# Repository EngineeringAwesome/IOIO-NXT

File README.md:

IOIO-NXT
========

A circuit board that breaks out the pins on a IOIO-OTG to connect to the NXT Socket.

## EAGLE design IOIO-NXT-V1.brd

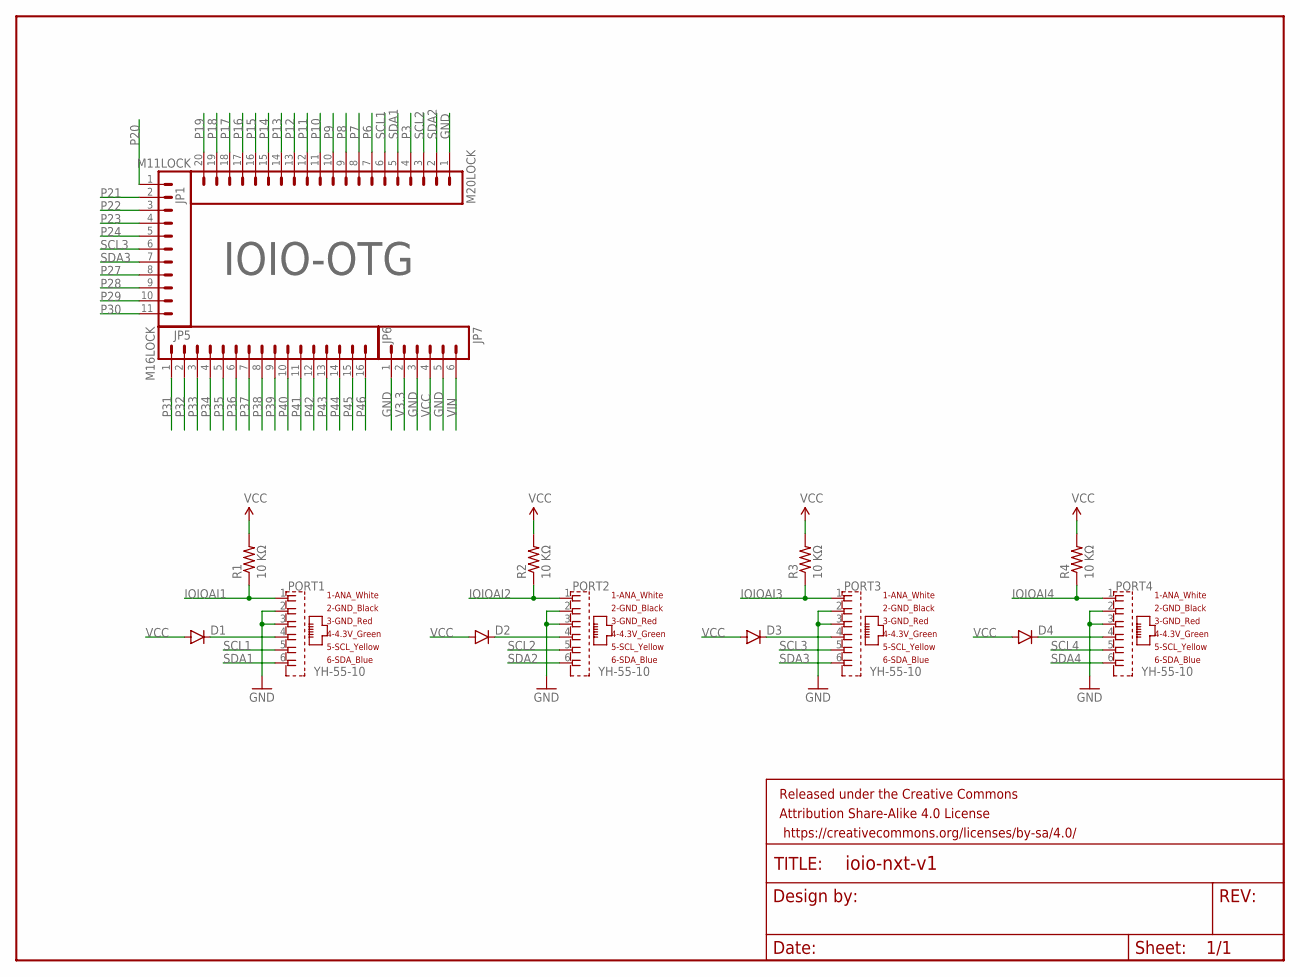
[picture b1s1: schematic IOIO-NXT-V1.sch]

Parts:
D1, D2, D3, D4: DIODE; DIODE-1N4001-KIT
FRAME1: FRAME-LETTER; CREATIVE_COMMONS
JP1: M20LOCK; 1X20_LOCK
JP5: M11LOCK; 1X11_LOCK
JP6: M16LOCK; 1X16_LOCK
JP7: M06LOCK; 1X06_LOCK
PORT1, PORT2, PORT3, PORT4: YH-55-10
R1, R2, R3, R4: 10 KΩ; AXIAL-0.4

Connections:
GND: JP1.1, JP7.1, JP7.3, JP7.5, PORT1.2 (2_GND_BLACK), PORT1.3 (3_GND_RED), PORT2.2 (2_GND_BLACK), PORT2.3 (3_GND_RED), PORT3.2 (2_GND_BLACK), PORT3.3 (3_GND_RED), PORT4.2 (2_GND_BLACK), PORT4.3 (3_GND_RED)
IOIOAI1: PORT1.1 (1_ANA_WHITE), R1.P$1 (1)
IOIOAI2: PORT2.1 (1_ANA_WHITE), R2.P$1 (1)
IOIOAI3: PORT3.1 (1_ANA_WHITE), R3.P$1 (1)
IOIOAI4: PORT4.1 (1_ANA_WHITE), R4.P$1 (1)
unnamed: D1.C, PORT1.4 (4_4.3V_GREEN)
unnamed: D4.C, PORT4.4 (4_4.3V_GREEN)
unnamed: D2.C, PORT2.4 (4_4.3V_GREEN)
unnamed: D3.C, PORT3.4 (4_4.3V_GREEN)
P3: JP1.4
P6: JP1.7
P7: JP1.8
P8: JP1.9
P9: JP1.10
P10: JP1.11
P11: JP1.12
P12: JP1.13
P13: JP1.14
P14: JP1.15
P15: JP1.16
P16: JP1.17
P17: JP1.18
P18: JP1.19
P19: JP1.20
P20: JP5.1
P21: JP5.2
P22: JP5.3
P23: JP5.4
P24: JP5.5
P27: JP5.8
P28: JP5.9
P29: JP5.10
P30: JP5.11
P31: JP6.1
P32: JP6.2
P33: JP6.3
P34: JP6.4
P35: JP6.5
P36: JP6.6
P37: JP6.7
P38: JP6.8
P39: JP6.9
P40: JP6.10
P41: JP6.11
P42: JP6.12
P43: JP6.13
P44: JP6.14
P45: JP6.15
P46: JP6.16
SCL1: JP1.6, PORT1.5 (5_SCL_YELLOW)
SCL2: JP1.3, PORT2.5 (5_SCL_YELLOW)
SCL3: JP5.6, PORT3.5 (5_SCL_YELLOW)
SCL4: PORT4.5 (5_SCL_YELLOW)
SDA1: JP1.5, PORT1.6 (6_SDA_BLUE)
SDA2: JP1.2, PORT2.6 (6_SDA_BLUE)
SDA3: JP5.7, PORT3.6 (6_SDA_BLUE)
SDA4: PORT4.6 (6_SDA_BLUE)
V3.3: JP7.2
VCC: D1.A, D2.A, D3.A, D4.A, JP7.4, R1.P$2 (2), R2.P$2 (2), R3.P$2 (2), R4.P$2 (2)
VIN: JP7.6

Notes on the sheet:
IOIO-OTG

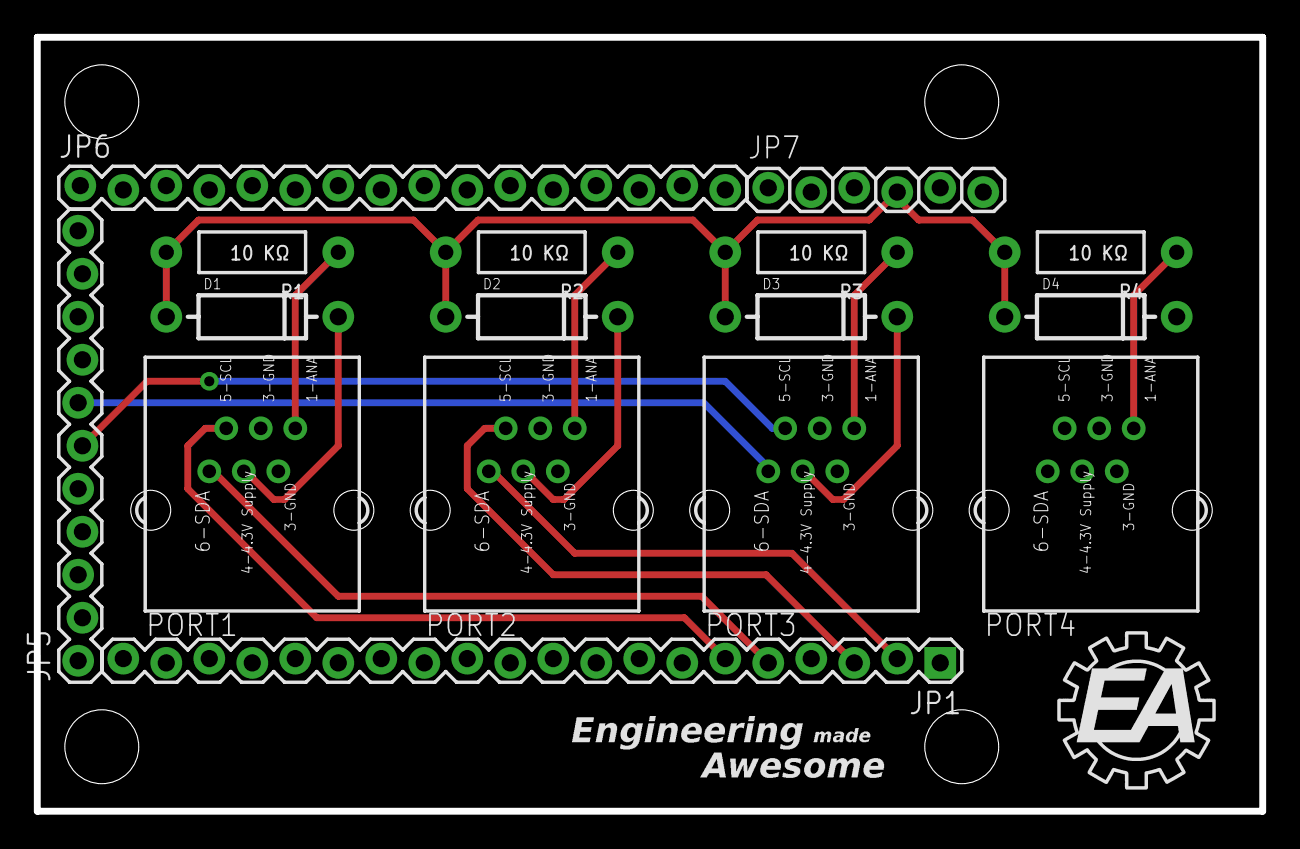
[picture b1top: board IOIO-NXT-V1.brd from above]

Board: 2 copper layers, 72.4 x 45.7 mm, 17 parts (0 on the bottom side), 16 nets.

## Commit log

2014-07-08 Added IOIO headers and EA logo. Waiting for analog pin #s
2015-10-30 Period
    Fixed punctuation.

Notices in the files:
parts and their libraries:
SparkFun-Aesthetics: Licensing: Creative Commons ShareAlike 4.0 International - https://creativecommons.org/licenses/by-sa/4.0
SparkFun-Aesthetics: Released under the Creative Commons Attribution Share-Alike 4.0 License
SparkFun-Aesthetics: https://creativecommons.org/licenses/by-sa/4.0
